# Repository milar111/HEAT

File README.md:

# HEAT – Smart Hot Plate Controller

> **⚠️ HIGH‑VOLTAGE WARNING**
>
> This project operates directly from **mains AC voltage (110–240 VAC)** and drives a high‑power resistive heater through a solid‑state relay (SSR).
>
> **Building, modifying, or operating this project is inherently dangerous.**
>
> * Mains voltage can cause **serious injury or death**.
> * Fire risk exists if wiring, insulation, grounding, or firmware safety logic is incorrect.
> * By building or using this project, **you take full responsibility for all risks**.
>
> The author provides this project **for educational purposes only** and assumes **no liability** for damages, injuries, or losses of any kind.

---

## 1. Project Overview

**HEAT** is a microcontroller‑based **smart hot‑plate / reflow heater controller** designed for electronics work such as SMD soldering, thermal experiments, and controlled heating tasks.

The system combines:

* A **STM32F103C8T6** microcontroller
* A **zero‑cross AC SSR** for safe mains switching
* A **100 kΩ NTC thermistor** for temperature feedback
* A **Smart Pulse & Coast control algorithm** (not classical PID)
* An **SSD1306 OLED UI** with buttons
* A **forced‑cooling fan** with safety logic
* Persistent settings storage in **internal flash**

---

## 2. System Architecture (High Level)

### 2.1 Functional Blocks

* **Power Input**

  * AC mains → AC‑DC module → 5 V → LDO → 3.3 V

* **Control Core**

  * STM32F103C8T6 running a cooperative main loop

* **Sensing**

  * NTC thermistor read via ADC

* **Actuation**

  * SSR for heater control (time‑proportional)
  * DC fan via MOSFET with software PWM

* **User Interface**

  * SSD1306 OLED (I²C)
  * Three buttons

* **Non‑Volatile Storage**

  * Internal Flash (last page)

---

## 3. Hardware Design

<table>
  <tr>
    <td>
      
    </td>
    <td>
      
    </td>
  </tr>
</table>

### 3.1 MCU Core

* **MCU:** STM32F103C8T6
* **Supply:** 3.3 V

Key reasons for choosing this MCU:

* Mature HAL support
* Adequate ADC performance
* Flash storage capability
* Simple debugging (SWD)

<table align="center">
  <tr>
    <td>
      
    </td>
    <td>
      
    </td>
  </tr>
</table>

---

### 3.2 Power Supply

#### AC-DC Conversion and Protection

* **AC-DC Module:** HLK-PM01 (isolated offline SMPS)
* **Input Voltage:** 110–240 VAC

**Input-side protection and conditioning (mains side):**

* **Fuse (1 A):** protects wiring and PCB against catastrophic faults and shorts.
* **MOV (varistor):** clamps high-voltage transients and spikes from the mains.
* **Bulk capacitor (220 nF, X2-rated):** reduces conducted EMI and high-frequency noise on the AC line.

**Output-side conditioning (low-voltage side):**

* **Electrolytic capacitor (220 µF, polarized):** provides bulk energy storage, reduces ripple, and stabilizes load transients from the MCU, fan, and SSR drive.

**Regulation:**

* **AMS1117-3.3 LDO:** drops 5 V to 3.3 V for the MCU and logic domain.

<table>
  <tr>
    <td>
      
    </td>
    <td>
      
    </td>
  </tr>
</table>

---

### 3.3 Heater & SSR Stage

#### Electrical Structure

* **Optotriac:** MOC3063M (zero-cross)
* **Power Triac:** BTA16-600B
* **Heater Power:** up to ~400 W resistive load
* **AC Fuse:** **3.15 A**, standard **6.3 × 32 mm (3AG)** cartridge

#### Fuse Placement and Purpose

The **3.15 A slow-blow fuse** on the heater line protects against:

* Triac failure (shorted MT1–MT2)
* Heater short circuits
* Wiring or connector faults

The slow-blow characteristic tolerates inrush current while still providing reliable fault protection.

#### How the SSR Works (Step-by-Step)

1. MCU GPIO drives the LED inside the MOC3063M
2. At the next AC zero crossing, the optotriac turns on
3. The optotriac triggers the gate of the BTA16 triac
4. The triac conducts AC current to the heater until the next zero crossing
5. Firmware decides when to enable or disable the optotriac

#### Time-Proportional Control

Instead of switching at mains frequency, the firmware uses **windowed control**:

* Fixed window: **250 ms**
* Heater ON for a percentage of that window

This approach is:

* SSR-safe
* Thermally smooth
* Simple and predictable

#### Interactive Simulation

Falstad simulaiton:

https://www.falstad.com/circuit/circuitjs.html?ctz=CQAgjCAMB0l3BWcMBMcUHYMGZIA4UA2ATmIxAUgpABZsKBTAWjDACg1DwMuwU9whKihpUxsSEhiJkVAGYBDADYBnBm1Hkm2FNy4694NgCcQxLiKpgaNEJaghsQk2d79wN8O6pPILlCJeAgG2YDwO2MRsAMZ2gWDEuiF2orTgzAIshNA0CMQ0hAgYxHwIhDR4ttKQEH6mLHyGTOWGVHR+AOYgTBVxtj3BqWJsAO7dvcnaSfhQo90tYVxTrXML4XhW3qu2aAIbKcNjLbseOzN+Y-v25gezY9Y7qYu3FyD7fAI3H3enQYbfr2e9mS9kB4W+yQBc0hiT6KzGkPcmF0UIRgWBGCSQzYKm6z2eLHczysIEUqnUY0JAgJrBR4T8ACU8eDPCxwY0xLQfNB6JyYAg5mzeOEhb8-AA3RwIFFIzF-ElCOy4BziAVgPAQZG3bDSl7gPAbaBEDXlYoVQgLOBecSSKCwAVjHUygROl5sAD2dnILTakFIjjQjiNDiS5GwHrsXB9XP9Om5KLskccbCAA

---

#### Why Zero-Cross Switching Matters for Heaters

The **MOC3063M** is a *zero-cross optotriac*, meaning it will only trigger the power triac when the AC waveform crosses **approximately 0 V**. Even if the MCU enables the optocoupler at an arbitrary time, the output remains inactive until a zero crossing occurs.

This behavior is critical for resistive heater loads:

- Switching at the voltage peak causes **large instantaneous current steps**
- These steps generate **EMI**, **audible noise**, and **electrical stress**
- Zero-cross turn-on ensures **minimum dv/dt and di/dt** at conduction start

The waveforms shown in the images demonstrate that random turn-on injects sharp current spikes, while zero-cross switching produces smooth sinusoidal current flow.

---

#### Why Phase-Angle Control Was Avoided

Phase-angle control deliberately turns the triac on mid-cycle. While useful for lamp dimming or motor speed control, it is **unsuitable for thermal systems**:

- Introduces significant EMI and harmonic distortion
- Increases thermal stress on the triac
- Requires complex timing logic synchronized to mains
- Provides no thermal benefit for a slow system like a heater

For heaters, only the **average power over time** matters—not instantaneous waveform shaping.

---

#### Zero-Cross + Time-Proportional Control

Because zero-cross optotriacs cannot modulate within a half-cycle, power is controlled using **time-proportional (windowed) control**:

- The firmware defines a fixed window (e.g. **250 ms**)
- The heater is enabled for a percentage of that window
- Each ON event starts at a zero crossing

This results in:

- Clean switching behavior
- Stable thermal output
- SSR-safe operation
- Predictable power delivery

The heater naturally integrates the power due to its thermal mass, eliminating the need for high-frequency modulation.

---

### 3.4 Thermistor Input

* **Type:** 100 kΩ NTC
* **Beta:** 3950
* **Divider:** 100 kΩ series resistor
* **ADC Reference:** 3.3 V

The firmware:

* Averages 16 ADC samples
* Applies a low‑pass filter
* Uses the Beta equation to convert resistance → temperature

---

### 3.5 Fan Driver

* **Fan type:** 5 V, 2-wire DC fan
* **MOSFET:** IRLML2502 (logic-level)
* **Flyback diode:** 1N5819

Because the fan is a **2-wire fan** (no tach, no PWM pin), speed control is implemented entirely in firmware using **software PWM**.

The PWM logic controls:

* Airflow rate
* Cooling aggressiveness
* Noise level

The firmware enforces:

* A minimum duty cycle where the fan reliably spins
* A short 100% startup boost to overcome static friction
* Full-speed override during cooling or fault conditions

---

### 3.6 OLED Display

* **Controller:** SSD1306
* **Resolution:** 128×64
* **Interface:** I²C @ 400 kHz

Pull‑ups:

* 2.2 kΩ on SDA/SCL

---

### 3.7 Buttons

* 3 momentary buttons
* Internal pull‑ups
* Active‑low

Used for:

* Start / Stop
* Navigation
* Editing values

---
## PCB Fabrication Notes

For PCB fabrication, the following stack-up has been tested and works reliably for this project:

- **Base material:** FR-4 S1000H (TG150)  
- **Copper thickness:** 1 oz  
- **Surface finish:** HASL (lead-free)  
- **Board thickness:** 1.6 mm  

If you want the **best no-compromise option**, especially for improved thermal stability, mechanical rigidity, and long-term reliability, I recommend:

- **Base material:** S1000-2M (TG170)  
- **Copper thickness:** 2 oz  
- **Surface finish:** ENIG  
- **Solder mask:** Black  
- **Board thickness:** 2.0 mm (optional but recommended)  

This configuration improves heat spreading, reduces copper resistance, and provides superior pad durability during repeated high-temperature operation.

---

## Electrical Safety Notice – Live Heatsink

> ⚠️ **IMPORTANT**
>
> The **heatsink attached to the triac is electrically live** and is directly connected to mains voltage.
>
> - Do **not** touch the heatsink while the device is powered.  
>
> Improper handling can result in **serious injury or electric shock**.

---
## 4. Firmware Architecture

### 4.1 File Structure

```
firmware/
├── main.c / main.h
├── control.c / control.h
├── heater.c / heater.h
├── fan.c / fan.h
├── thermistor.c / thermistor.h
├── ssd1306.c / ssd1306.h
├── ui.c / ui.h
├── storage.c / storage.h
```

---

### 4.2 Execution Model

* Single main loop
* No RTOS
* Deterministic timing via HAL_GetTick()
* ISR only used for fan PWM timing

**Main loop order:**

1. `Control_Update()`
2. `Heater_Update()`
3. `UI_Task()`

---

### 4.3 Control Module (`control.c`)

This module is the **central decision-making unit** of the entire system. All other subsystems react to values produced here.

#### Responsibilities

* Read raw temperature from the thermistor module
* Filter temperature readings
* Detect sensor failures
* Enforce absolute safety limits
* Execute the heating state machine
* Output a **heater power percentage** (0–100%)

No hardware is driven directly from this module. Instead, it produces *intent* values that other modules act upon.

---

### Control Timing

* Update period: **100 ms**
* Time base: `HAL_GetTick()`

Each control cycle performs the following steps **in strict order**:

1. Read raw temperature
2. Validate sensor range
3. Apply low-pass filtering
4. Check over-temperature cutoff
5. Run the heating state machine
6. Compute heater power percentage

If **any safety condition fails**, the module immediately:

* Sets heater power to 0%
* Forces the system into IDLE

---

### Why PID Was Abandoned

Early versions of the firmware used a classic PID controller with extensive tuning.

Despite significant tuning effort, the best achievable result still produced **~25 °C overshoot**.

Root causes:

* Heater power: ~400 W
* Plate mass: ~30 g
* Extremely fast thermal rise
* Significant thermal delay between heater and NTC

The thermistor simply could not observe the temperature rise quickly enough, causing the PID to react too late.

This led to the current solution: **Smart Pulse & Coast**, which is slower by design but **far more precise and repeatable**.

| State    | Meaning                 |
|----------|-------------------------|
| IDLE     | Waiting                 |
| HEATING  | Rising to setpoint      |
| HOLDING  | Maintaining temperature |
| COOLING  | Forced cooldown         |
| DONE     | Cycle finished          |

### 4.4 Smart Pulse & Coast Algorithm

This control method explicitly accounts for **thermal inertia and delay**.

Instead of continuously adjusting output, the heater is driven in **full-power pulses**, followed by observation periods.

#### Core Idea

1. Apply a controlled heat pulse
2. Turn the heater fully off
3. Observe how temperature continues to rise
4. Decide the next pulse based on real thermal response

This prevents the controller from "chasing" delayed measurements.

#### Pulse Zones

Pulse width is selected based on the ratio:

```
current_temperature / setpoint
```

| Zone | Ratio  | Pulse Width |
| ---- | ------ | ----------- |
| Far  | < 70%  | 2000 ms     |
| Mid  | 70–85% | 500 ms      |
| Near | > 85%  | 250 ms      |

#### Coast Phase Logic

During the coast phase:

* Heater is guaranteed OFF
* The firmware tracks the **peak temperature**
* A new pulse is allowed only after:

  * A minimum wait time has passed **and**
  * Temperature has begun to fall

This ensures the full thermal effect of each pulse is observed.

---

### 4.5 Heater Power, Mass, and Thermal Reality

To understand why the control strategy must be conservative, it helps to look at the **physics of the heater–plate system**.

#### Ideal Electrical Power Calculation

Even thoough the heater is listed as 400W, it was measured to have an approximate **cold resistance of 340 Ω**.

Using Ohm’s law:

```
P = V² / R
```

For a 230 V RMS mains supply:

```
P = (230 V)² / 340 Ω ≈ 155 W
```

This calculation is **electrically correct** and provides a useful order-of-magnitude estimate.

#### Why This Value Is Not Reliable in Practice

Although the formula is correct, it is **not something the control system can rely on precisely**, for several reasons:

1. **Resistance changes with temperature**
   Heating elements increase resistance as they get hotter. The 340 Ω value is a cold measurement and rises significantly during operation.

2. **Mains voltage is not constant**
   Real-world mains can vary by ±10% or more, directly affecting power.

3. **Thermal coupling dominates behavior**
   The system response is governed by how fast heat flows into the plate, not by instantaneous electrical power.

4. **Plate mass is very small**
   The aluminum plate mass is approximately **30 g**, which means:

   * Temperature rises extremely fast
   * Small energy pulses produce large temperature changes

#### Energy Perspective (Why Overshoot Happens)

The temperature rise of the plate is governed by:

```
ΔT = Q / (m · c)
```

Where:

* `Q` = heat energy (J)
* `m` = mass (kg)
* `c` = specific heat capacity (J/kg·K)

With:

* `m ≈ 0.03 kg`
* Aluminum `c ≈ 900 J/kg·K`

Even a **short, high-power pulse** injects enough energy to raise the temperature dramatically before the thermistor can respond.

This is the fundamental reason why:

* PID control overshot by ~25 °C
* Slower, observation-based control is required

The Smart Pulse & Coast approach deliberately limits **energy per pulse**, making the system predictable even when electrical power and resistance vary.

---

### 4.5 Heater Module (`heater.c`)

* Implements time‑windowed SSR control
* Enforces immediate OFF on any error

**Return behavior:**

* No return value
* Acts directly on GPIO

---

### 4.6 Fan Module (`fan.c`)

* Software PWM via TIM2
* Emergency override logic

Conditions forcing 100%:

* Cooling phase
* Sensor error
* Over‑temperature
* Temperature freeze detection

---

### 4.7 Thermistor Module (`thermistor.c`)

* ADC averaging
* Beta equation

`Thermistor_ReadTemperatureC()` returns:

* Temperature in °C
* Raw (unfiltered)

---

### 4.8 UI Module (`ui.c`)

Provides three screens:

1. **Status**

   * Current temp
   * Target
   * Heater power
   * Fan power

2. **Settings**

   * Setpoint
   * PID values (future‑proofing)
   * Max temperature
   * Hold time

3. **Graph**

   * Live temperature plot
   * Setpoint overlay

---

### 4.9 Storage Module (`storage.c`)

* Uses last flash page (0x0800FC00)
* Stores struct with magic number

Saved parameters:

* Setpoint
* PID values
* Max temperature
* Hold time

---

## 5. File Interaction Graph

To visualize module interactions, generate a graph using:

* **Graphviz**
* **Doxygen** with call graphs

Example idea:

```
control → heater
control → fan
control → ui
ui → storage
storage → control
thermistor → control
```

---

## 6. Cable Length & Wiring (As Built)

The following cable lengths reflect the **actual physical implementation** of the current build.

| Connection       | Cable Length |
| ---------------- | ------------ |
| Thermistor → PCB | ~160 cm       |
| OLED (I²C) → PCB | ~51 mm       |
| Buttons → PCB    | ~130 mm       |
| Fan → PCB        | ~120 mm       |
| AC inlet → PCB   | ~75 mm       |  
| AC inlet Earth → PCB   | ~115 mm       |  

---
## 7. Enclosure, Printing, and Mechanical Assembly

<table>
  <tr>
    <td>
      
    </td>
    <td>
      
    </td>
  </tr>
</table>

### Enclosure Material and Printing

The enclosure is **3D printed from ASA**.

ASA was chosen because:
- It has **much better heat resistance** than PLA
- It is **dimensionally stable** near warm electronics and heater-adjacent areas
- It offers **good mechanical strength** while remaining printable on consumer printers
- It is **UV- and heat-resistant**, making it suitable for long-term use

PLA was intentionally avoided because it softens at relatively low temperatures and would deform over time in this application.

**Print settings used:**
- **Layer height:** 0.2 mm
- **Material:** ASA
- **Infill / walls:** standard structural settings (not critical to functionality)

### Optional Embedded Nut Reinforcement

<table>
  <tr>
    <td>
      
    </td>
    <td>
      
    </td>
    <td>
      
    </td>
  </tr>
</table>

At **layer 155** (optional), the print can be **paused** to insert **M4 nuts** directly into the enclosure.

- **Nut type:** M4 hex nut
- **Across flats:** 6.9 mm
- **Height:** 3 mm
- **Orientation:** inserted from side to side into the printed cavities

This reinforcement:
- Significantly increases mechanical rigidity
- Improves long-term durability
- Makes the enclosure feel substantially more solid

#### If You Do Not Insert Nuts

The enclosure is designed so that:
- The heater mounting holes are placed **slightly inward**
- This creates **mechanical tension** that can hold the heater assembly even **without screws**

This approach:
- **Works**, and the device can be assembled without embedded nuts
- Is **not ideal**, as the structure:
  - Feels less rigid
  - Is more prone to loosening or disassembly over time

For best results, inserting the nuts is strongly recommended.

---

### Fasteners and Hardware Used

| Application                              | Fastener Used                     |
|------------------------------------------|-----------------------------------|
| Heater mounting                          | M4 × 60 mm bolts + M4 lock nuts   |
| Fan mounting                             | M3 × 30 mm bolts + M3 lock nuts   |
| Power inlet mounting                     | M3 × 16 mm screws + M3 lock nuts  |
| Triac → heatsink connection              | M3 × 10 mm bolt                  |
| Protective earth (ground) connection     | Wire to heater bolt using 2× M4 lock nuts + 2× M4 washers|

The grounding wire needs to be stripped and bent into a hook shape so that it can later be inserted under one of the heater’s legs (the M4 bolt).

---
### Quick assembly
1. Solder Peripherals: Before mounting the PCB, solder the wires for the thermistor, fan, OLED display, and buttons to their respective pads on the board.
2. Place PCB in Enclosure: Insert the PCB into the bottom of the case.
Pro Tip: If you soldered the button wires to the bottom side of the PCB (highly recommended), the tension created by the wires will allow the PCB to "snap" perfectly into position and hold itself securely without needing hot glue.
3. Connect AC Inlet: Solder the wires from the AC Power Socket to the AC IN pads on the PCB.
⚠️ IMPORTANT: Perform this soldering with the PCB in a vertical position (lifted out of the case). If you try to solder these pads from above while the PCB is sitting flat inside, the heat will melt and destroy the 3D-printed enclosure walls.
4. Secure UI Components:
OLED: Use a small amount of glue to secure the display to the front panel.
Buttons: Push the tactile buttons into their housing. If you used the specific 5.5mm x 6mm buttons listed, they should fit snugly without needing glue.
5. Protective Grounding: Connect the Earth/Ground wire from the AC inlet directly to one of the heater's m4 bolts. Secure it tightly with washers and lock nuts to ensure the heater plate is grounded.
6. Secure the Fan Mount the fan into its dedicated slot in the enclosure and secure it with M3 screws.
7. Mount the Heater Insert the four M4 × 60mm bolts into the heater block and lower it onto the enclosure.
If you used the embedded nuts method during printing, simply screw the bolts into the case.
8. Install Thermistor Tuck the NTC thermistor head into the small hole on the heater block.

---

## 8. Parts and External Resources

The table below contains links to the main components used in this project.  

| Component / Resource | Description | Link |
|---------------------|-------------|------|
| Heater | AC resistive heater (400 W - 220V) | [LINK](https://www.aliexpress.com/item/1005007420346819.html?spm=a2g0o.order_list.order_list_main.74.5d041802ybo8pW) |
| Thermistor | 100 kΩ NTC, Beta ≈ 3950 | [LINK](https://www.aliexpress.com/item/1005006897238013.html?spm=a2g0o.order_list.order_list_main.79.5d041802ybo8pW) |
| OLED Display | SSD1306, 128×64, I²C | [LINK](https://www.aliexpress.com/item/1005006365875586.html?spm=a2g0o.order_list.order_list_main.186.5d041802ybo8pW) |
| Fan | 5 V, 2-wire DC fan | [LINK](https://www.aliexpress.com/item/1005006306536871.html?spm=a2g0o.order_list.order_list_main.5.5d041802ybo8pW) |
| Buttons | 5.5mm x 6mm |  |
| 3.15 A, standard 6.3 × 32 mm (3AG) cartridge| FUSE |  |

# Interactive BOM (iBOM)

This project includes an **interactive Bill of Materials (iBOM)** generated directly from the PCB design.

The iBOM allows you to:
- Inspect all components directly on the PCB
- Click a part to see its reference, value, and footprint
- Highlight parts on the board from the BOM list
- Better understand component placement and assembly

You can access the interactive BOM here:

➡️ **[Open the Interactive BOM](https://heat-delta.vercel.app)**

---
## 9. Licensing

```
License

Documentation in this repository, including this README, is licensed under
Creative Commons Attribution–NonCommercial–ShareAlike 4.0 (CC BY-NC-SA).

Hardware design files are located in /hardware and are licensed under
the same license.

Firmware source code is located in /firmware and licensed under GNU GPL v3.
```

---

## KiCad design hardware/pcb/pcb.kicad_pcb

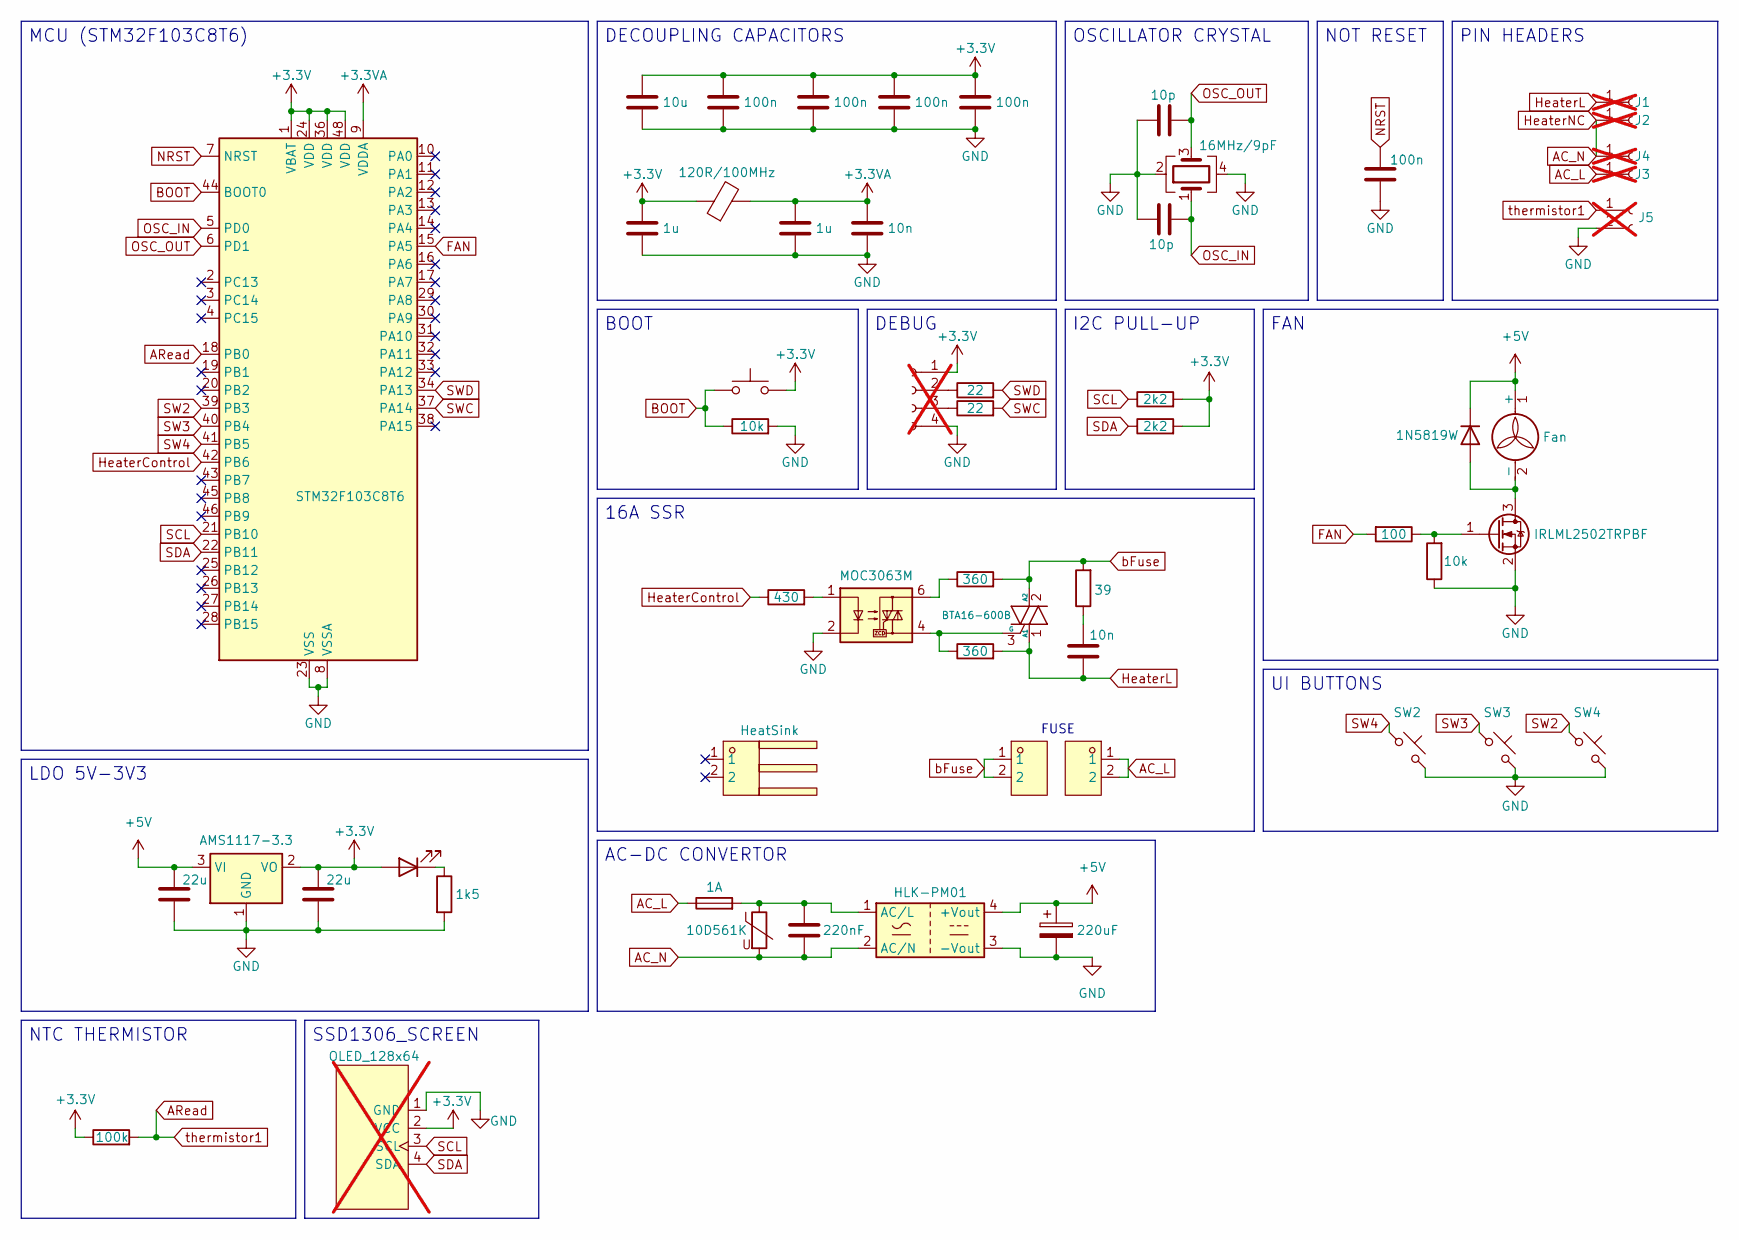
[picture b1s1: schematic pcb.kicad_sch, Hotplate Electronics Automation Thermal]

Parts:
C1: 10u; C_0805_2012Metric_Pad1.18x1.45mm_HandSolder; LCSC Part C15850
C2, C3, C4, C5, C7: 100n; C_0402_1005Metric_Pad0.74x0.62mm_HandSolder; LCSC Part C155422
C6, C8: 10p; C_0402_1005Metric_Pad0.74x0.62mm_HandSolder; LCSC Part C76946
C9, C10: 1u; C_0603_1608Metric_Pad1.08x0.95mm_HandSolder; LCSC Part C15849
C11, C14: 10n; C_0402_1005Metric_Pad0.74x0.62mm_HandSolder; LCSC Part C15195
C12: 220nF; CAP-TH_L18.0-W7.5-P15.00-D0.8; LCSC Part C2848140
C13: 220uF; CP_Radial_D6.3mm_P2.50mm; LCSC Part C338177
C15, C16: 22u; C_0805_2012Metric_Pad1.18x1.45mm_HandSolder; LCSC Part C602037
D1: BLUE; LED_0603_1608Metric_Pad1.05x0.95mm_HandSolder; LCSC Part C965807
D2: 1N5819W; D_SOD-123; LCSC Part C963381
F1: 1A; F2410; LCSC Part C136380
FB1: 120R/100MHz; L_0603_1608Metric_Pad1.05x0.95mm_HandSolder; LCSC Part C14709
FH1, FH2: LS-601; FUSE-TH_LS-601; LCSC Part C182321
HT1: HeatSink; HEATSINK-TH_L16.5-W16.0-P10.00-D1.5; LCSC Part C286228
J1, J2, J3, J4: Conn_01x01_Socket; PinHeader_1x01_P2.54mm_Vertical; not fitted
J5: Conn_01x02_Socket; PinHeader_1x02_P2.54mm_Vertical; not fitted
J6: Conn_01x04_Socket; PinHeader_1x04_P2.54mm_Vertical; not fitted
J7: OLED_128x64; not fitted
M1: Fan; PinHeader_1x02_P2.54mm_Vertical
PS1: HLK-PM01; Converter_ACDC_HiLink_HLK-PMxx; LCSC Part C209903
Q1: BTA16-600B; TO-220-3_Vertical; LCSC Part C19184934
Q2: IRLML2502TRPBF; SOT-23; LCSC Part C2589
R1, R3: 22; R_0402_1005Metric_Pad0.72x0.64mm_HandSolder; LCSC Part C114765
R2, R5: 2k2; R_0402_1005Metric_Pad0.72x0.64mm_HandSolder; LCSC Part C25879
R4, R14: 10k; R_0603_1608Metric_Pad0.98x0.95mm_HandSolder; LCSC Part C98220
R6, R9: 360; R_0603_1608Metric_Pad0.98x0.95mm_HandSolder; LCSC Part C25194
R7: 39; R_0603_1608Metric_Pad0.98x0.95mm_HandSolder; LCSC Part C2907032
R8: 430; R_0603_1608Metric_Pad0.98x0.95mm_HandSolder; LCSC Part C137721
R11: 1k5; R_0603_1608Metric_Pad0.98x0.95mm_HandSolder; LCSC Part C22843
R12: 100k; R_0603_1608Metric_Pad0.98x0.95mm_HandSolder; LCSC Part C14675
R13: 100; R_0603_1608Metric_Pad0.98x0.95mm_HandSolder; LCSC Part C105588
RV1: 10D561K; RES-TH_L9.0-W5.5-P7.50-D0.6-S4.00; LCSC Part C2839517
SW1: SW_Push; SW-SMD_L3.9-W3.0-P4.45; LCSC Part C455280
SW2, SW3, SW4: SW_Push_45deg; SW-SMD_L3.9-W3.0-P4.45; LCSC Part C455280
U1: STM32F103C8T6; LQFP-48_7x7mm_P0.5mm; LCSC Part C8734
U2: MOC3063M; DIP-6_L8.5-W6.4-P2.54-LS7.6-BL; LCSC Part C8920
U3: AMS1117-3.3; SOT-223-3_TabPin2; LCSC Part C6186
Y1: 16MHz/9pF; Crystal_SMD_3225-4Pin_3.2x2.5mm; LCSC Part C13738

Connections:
+3.3V: C1.1, C2.1, C3.1, C4.1, C5.1, C9.1, C16.1, D1.2 (A), FB1.1, J6.1, J7.2 (VCC), R2.2, R5.2, R12.1, SW1.2, U1.1 (VBAT), U1.24 (VDD), U1.36 (VDD), U1.48 (VDD), U3.2 (VO)
+3.3VA: C10.1, C11.1, FB1.2, U1.9 (VDDA)
+5V: C13.1, C15.1, D2.1 (K), M1.1 (+), PS1.4 (+Vout), U3.3 (VI)
AC_L: F1.1, FH2.1, FH2.2, J3.1
AC_N: C12.2, J2.1, J4.1, PS1.2 (AC/N), RV1.2
ARead: J5.1, R12.2, U1.18 (PB0)
BOOT: R4.1, SW1.1, U1.44 (BOOT0)
FAN: R13.2, U1.15 (PA5)
GND: C1.2, C2.2, C3.2, C4.2, C5.2, C6.2, C7.2, C8.2, C9.2, C10.2, C11.2, C13.2, C15.2, C16.2, J5.2, J6.4, J7.1 (GND), PS1.3 (-Vout), Q2.2 (S), R4.2, R11.2, R14.1, SW2.2, SW3.2, SW4.2, U1.8 (VSSA), U1.23 (VSS), U1.35 (VSS), U1.47 (VSS), U2.2, U3.1 (GND), Y1.2, Y1.4
HeaterControl: R8.1, U1.42 (PB6)
HeaterL: C14.2, J1.1, Q1.1 (A1), R9.2
NRST: C7.1, U1.7 (NRST)
unnamed: C14.1, R7.1
unnamed: D1.1 (K), R11.1
unnamed: D2.2 (A), M1.2 (-), Q2.3 (D)
unnamed: J6.2, R1.1
unnamed: J6.3, R3.1
unnamed: C12.1, F1.2, PS1.1 (AC/L), RV1.1
unnamed: Q1.3 (G), R9.1, U2.4
unnamed: Q2.1 (G), R13.1, R14.2
unnamed: R6.1, U2.6
unnamed: R8.2, U2.1
OSC_IN: C8.1, U1.5 (PD0), Y1.1
OSC_OUT: C6.1, U1.6 (PD1), Y1.3
SCL: J7.3 (SCL), R2.1, U1.21 (PB10)
SDA: J7.4 (SDA), R5.1, U1.22 (PB11)
SW2: SW4.1, U1.39 (PB3)
SW3: SW3.1, U1.40 (PB4)
SW4: SW2.1, U1.41 (PB5)
SWC: R3.2, U1.37 (PA14)
SWD: R1.2, U1.34 (PA13)
bFuse: FH1.1, FH1.2, Q1.2 (A2), R6.2, R7.2

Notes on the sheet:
FUSE
NOT RESET
16A SSR
UI BUTTONS
AC-DC CONVERTOR
FAN
SSD1306_SCREEN
DECOUPLING CAPACITORS
DEBUG
I2C PULL-UP
MCU (STM32F103C8T6)
LDO 5V-3V3
PIN HEADERS
NTC THERMISTOR
OSCILLATOR CRYSTAL
BOOT

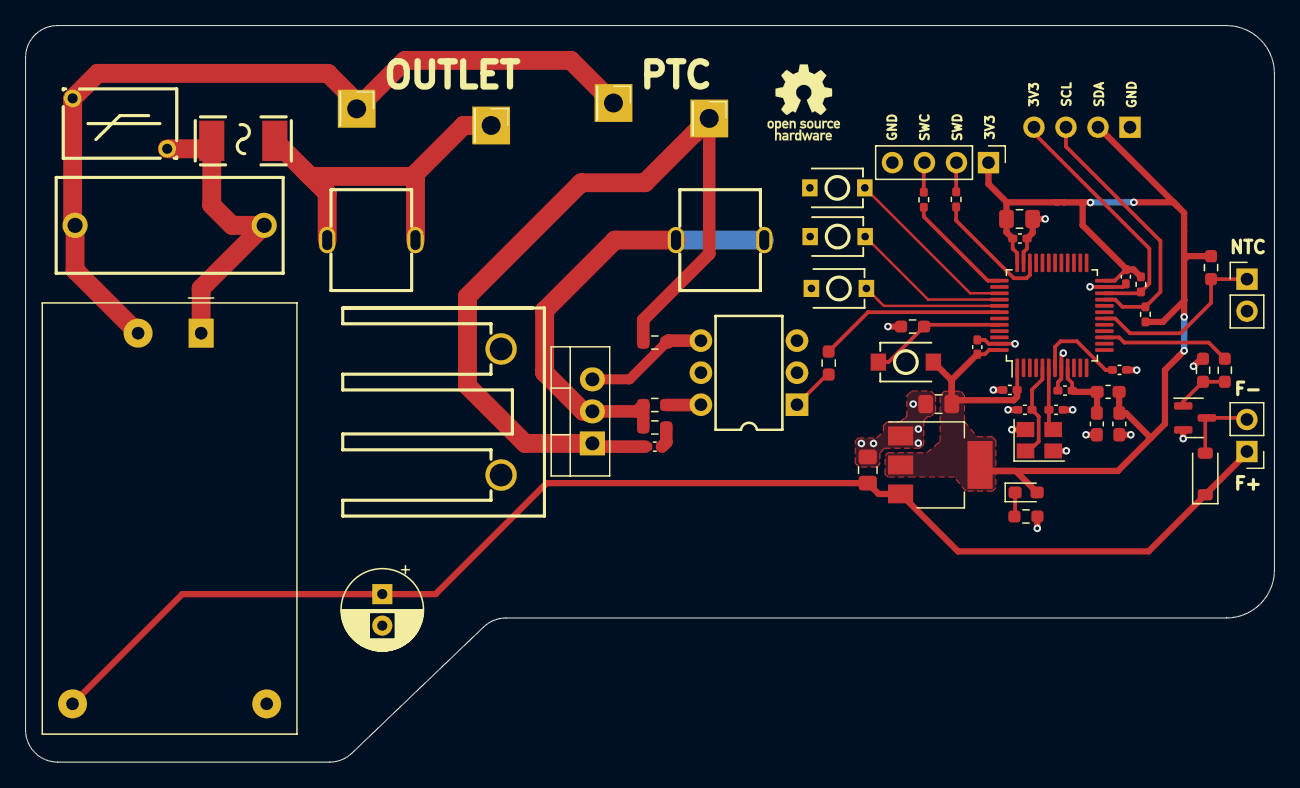
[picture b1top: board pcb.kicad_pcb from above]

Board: 2 copper layers, 99.1 x 58.4 mm, 56 parts (0 on the bottom side), 32 nets.

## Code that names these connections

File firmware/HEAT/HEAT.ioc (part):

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Mcu.Name=STM32F103C(8-B)Tx
Mcu.Package=LQFP48
Mcu.UserName=STM32F103C8Tx
PA13.Mode=Serial_Wire
PA13.Signal=SYS_JTMS-SWDIO
PA14.Mode=Serial_Wire
PA14.Signal=SYS_JTCK-SWCLK
PA5.Signal=GPIO_Output
PB0.Signal=ADCx_IN8
PB10.Mode=I2C
PB10.Signal=I2C2_SCL
PB11.Mode=I2C
PB11.Signal=I2C2_SDA
PB3.GPIOParameters=GPIO_PuPd
PB3.GPIO_PuPd=GPIO_PULLUP
PB3.Signal=GPIO_Input
PB4.GPIOParameters=GPIO_PuPd
PB4.GPIO_PuPd=GPIO_PULLUP
PB4.Signal=GPIO_Input
PB5.GPIOParameters=GPIO_PuPd
PB5.GPIO_PuPd=GPIO_PULLUP
PB5.Signal=GPIO_Input
PB6.Signal=GPIO_Output
PD0-OSC_IN.Mode=HSE-External-Oscillator
PD0-OSC_IN.Signal=RCC_OSC_IN
PD1-OSC_OUT.Mode=HSE-External-Oscillator
PD1-OSC_OUT.Signal=RCC_OSC_OUT
RCC.HSEDivPLL=RCC_HSE_PREDIV_DIV2
RCC.HSE_VALUE=16000000
board=custom

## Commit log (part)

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2025-12-30 3d files, firmware, pcb files
2025-12-30 Create README.md with project overview and details
    Added detailed project documentation including safety warnings, system architecture, hardware design, firmware architecture, and licensing information.
2026-01-01 images not loading README
2026-01-01 Enhance README with assembly steps and grounding info
    Added quick assembly instructions and updated grounding details.
2026-01-01 heat.stl
